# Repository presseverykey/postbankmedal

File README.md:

# POST /bank Hackathon Roadshow Medal

This repository contains hardware documentation (Eagle files and PDF) and firmware sources (C) for the medals given to winners at the POST /bank hackathon series 2016/2017 Grand Final.

The actual boards given out differ in two points:
- MCU ground connections (Pins 5 and 41) are missing on the board due to a PCB manufacturing error. They are manually routed using wire.
- Due to a worldwide supply shortage of TBD62083 drivers, the boards are populated with a TBD62003 chip (7 channels instead of 8). The remaining channel is populated with a 2N7000 NMOS on top of the TBD62003.

The board has pads for a resistive and a capacitive touch sensor, however, they are not used in the current firmware.

The firmware is based on the everykey SDK (see https://github.com/presseverykey/everykey-sdk for prerequisites, toolchain setup and more examples). Basically, an ARM GCC cross compiler and a firmware checksum tool is required. The MCU supports flashing via USB mass storage in ROM, so no additional flashing hardware is required. The firmware binary can be just copied over. To enable flashing mode, press the button while inserting the board to a USB port (add 0.5-1mm of cardboard or similar under the PCB for a stable connection). Some OSes will mount the drive directly, some require an additional reset. If required, a MCU reset can be triggered by connecting the corresponding pad of R5 to GND, e.g. using metal tweezers.

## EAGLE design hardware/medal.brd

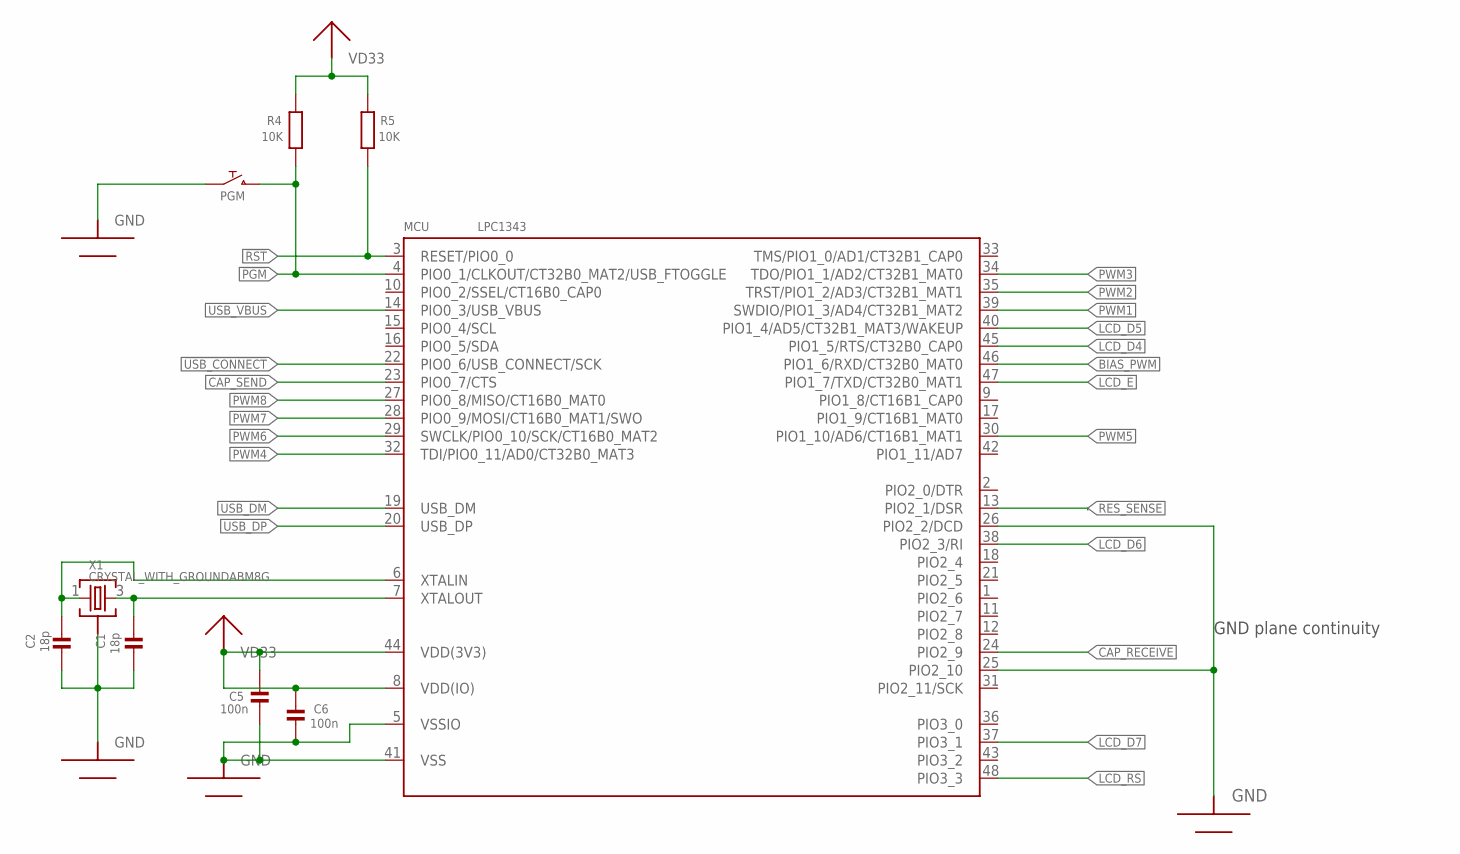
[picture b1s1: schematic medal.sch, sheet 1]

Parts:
C1, C2: 18p; 0603-NOSILK
C5, C6: 100n; 0603-NOSILK
MCU: LPC1343; QFP48-0.5-NOSILK
PGM: PUSHBUTTONKMR2XX-NOSILK; CK-KMR2-NOSILK
R4, R5: 10K; 0603-NOSILK
X1: CRYSTAL_WITH_GROUNDABM8G; ABM8G

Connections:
!PGM: MCU.4 (PIO0_1/CLKOUT/CT32B0_MAT2/USB_FTOGGLE), PGM.P$3 (2), PGM.P$4 (2), R4.1
!RST: MCU.3 (RESET/PIO0_0), R5.1
!USB_CONNECT: MCU.22 (PIO0_6/USB_CONNECT/SCK); also elsewhere on the board
BIAS_PWM: MCU.46 (PIO1_6/RXD/CT32B0_MAT0); also elsewhere on the board
CAP_RECEIVE: MCU.24 (PIO2_9); also elsewhere on the board
CAP_SEND: MCU.23 (PIO0_7/CTS); also elsewhere on the board
GND: C1.1, C2.1, C5.2, C6.2, MCU.5 (VSSIO), MCU.25 (PIO2_10), MCU.26 (PIO2_2/DCD), MCU.41 (VSS), PGM.P$1 (1), PGM.P$2 (1), X1.2 (GND), X1.4 (GND); also elsewhere on the board
LCD_D4: MCU.45 (PIO1_5/RTS/CT32B0_CAP0); also elsewhere on the board
LCD_D5: MCU.40 (PIO1_4/AD5/CT32B1_MAT3/WAKEUP); also elsewhere on the board
LCD_D6: MCU.38 (PIO2_3/RI); also elsewhere on the board
LCD_D7: MCU.37 (PIO3_1); also elsewhere on the board
LCD_E: MCU.47 (PIO1_7/TXD/CT32B0_MAT1); also elsewhere on the board
LCD_RS: MCU.48 (PIO3_3); also elsewhere on the board
unnamed: C2.2, MCU.6 (XTALIN), X1.1
unnamed: C1.2, MCU.7 (XTALOUT), X1.3 (2)
PWM1: MCU.39 (SWDIO/PIO1_3/AD4/CT32B1_MAT2); also elsewhere on the board
PWM2: MCU.35 (TRST/PIO1_2/AD3/CT32B1_MAT1); also elsewhere on the board
PWM3: MCU.34 (TDO/PIO1_1/AD2/CT32B1_MAT0); also elsewhere on the board
PWM4: MCU.32 (TDI/PIO0_11/AD0/CT32B0_MAT3); also elsewhere on the board
PWM5: MCU.30 (PIO1_10/AD6/CT16B1_MAT1); also elsewhere on the board
PWM6: MCU.29 (SWCLK/PIO0_10/SCK/CT16B0_MAT2); also elsewhere on the board
PWM7: MCU.28 (PIO0_9/MOSI/CT16B0_MAT1/SWO); also elsewhere on the board
PWM8: MCU.27 (PIO0_8/MISO/CT16B0_MAT0); also elsewhere on the board
RES_SENSE: MCU.13 (PIO2_1/DSR); also elsewhere on the board
USB_DM: MCU.19 (USB_DM); also elsewhere on the board
USB_DP: MCU.20 (USB_DP); also elsewhere on the board
USB_VBUS: MCU.14 (PIO0_3/USB_VBUS); also elsewhere on the board
VD33: C5.1, C6.1, MCU.8 (VDD(IO)), MCU.44 (VDD(3V3)), R4.2, R5.2; also elsewhere on the board

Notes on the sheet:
GND plane continuity

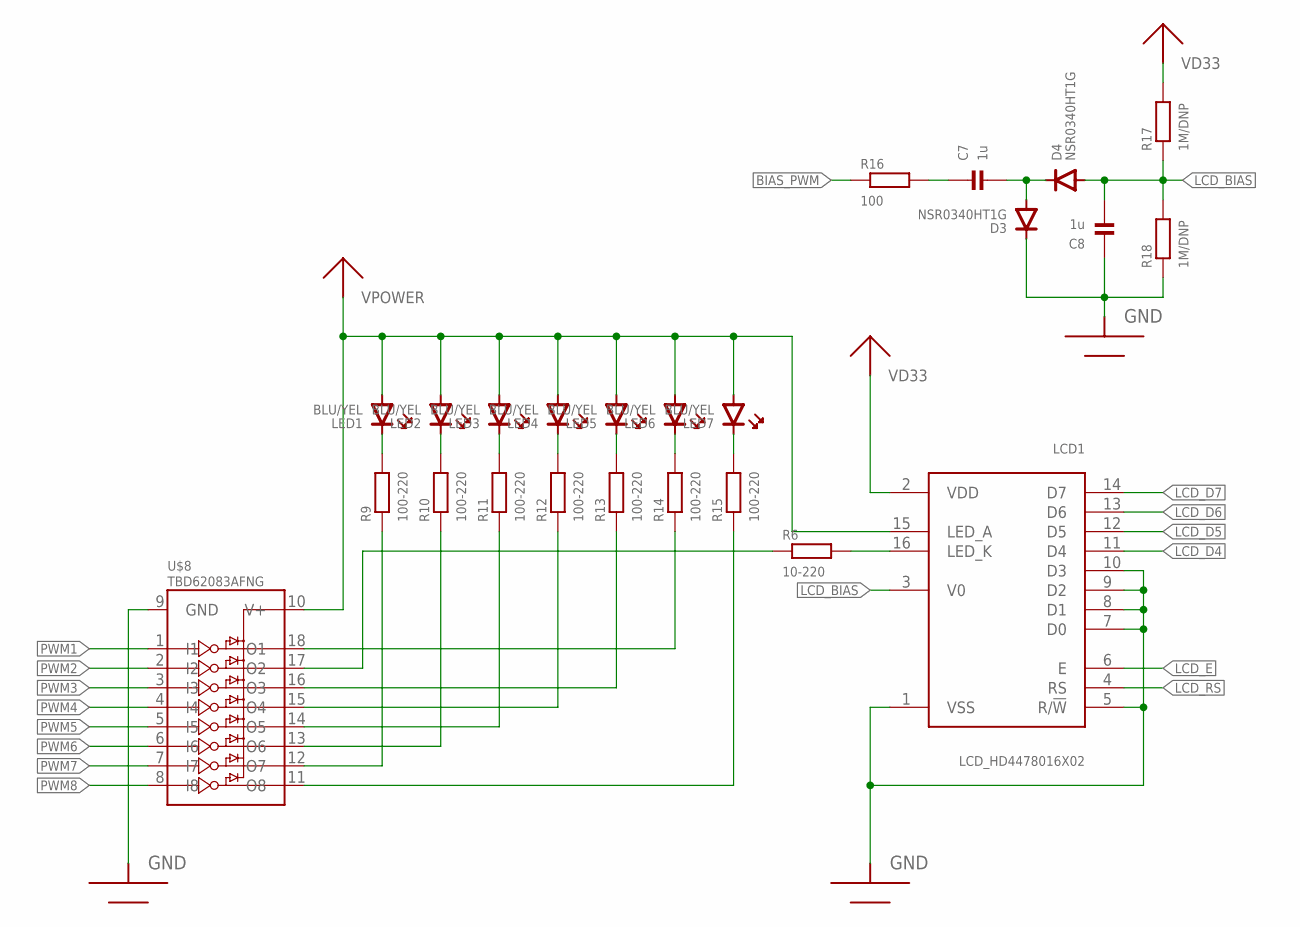
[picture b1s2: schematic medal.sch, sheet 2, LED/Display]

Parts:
C7, C8: 1u; 0603-NOSILK
D3, D4: NSR0340HT1G; SOD323R-NOPLACE
LCD1: LCD_HD4478016X02; LCD_16X02
LED1, LED2, LED3, LED4, LED5, LED6, LED7: BLU/YEL; 0603_POLAR
R6: 10-220; 1206-NOSILK
R9, R10, R11, R12, R13, R14, R15: 100-220; 0603-NOSILK
R16: 100; 0603-NOSILK
R17, R18: 1M/DNP; 0603-NOSILK
U$8: TBD62083AFNG; SSOP18-4.4-0.65-NOPLACE

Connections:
BIAS_PUMP: C7.2, D3.A (ANODE), D4.K (CATHODE)
BIAS_PWM: R16.1; also elsewhere on the board
BIAS_PWM_LIM: C7.1, R16.2
GND: C8.1, D3.K (CATHODE), LCD1.1 (VSS), LCD1.5 (R/!W), LCD1.7 (D0), LCD1.8 (D1), LCD1.9 (D2), LCD1.10 (D3), R18.1, U$8.9 (GND); also elsewhere on the board
LCD_BIAS: C8.2, D4.A (ANODE), LCD1.3 (V0), R17.1, R18.2
LCD_D4: LCD1.11 (D4); also elsewhere on the board
LCD_D5: LCD1.12 (D5); also elsewhere on the board
LCD_D6: LCD1.13 (D6); also elsewhere on the board
LCD_D7: LCD1.14 (D7); also elsewhere on the board
LCD_E: LCD1.6 (E); also elsewhere on the board
LCD_RS: LCD1.4 (RS); also elsewhere on the board
unnamed: R6.1, U$8.17 (O2)
unnamed: LCD1.16 (LED_K), R6.2
unnamed: R13.1, U$8.16 (O3)
unnamed: R10.1, U$8.13 (O6)
unnamed: LED1.K (CATHODE), R9.2
unnamed: LED2.K (CATHODE), R10.2
unnamed: LED3.K (CATHODE), R11.2
unnamed: LED4.K (CATHODE), R12.2
unnamed: LED5.K (CATHODE), R13.2
unnamed: LED6.K (CATHODE), R14.2
unnamed: LED7.K (CATHODE), R15.2
OC2: R9.1, U$8.12 (O7)
OC4: R11.1, U$8.14 (O5)
OC5: R12.1, U$8.15 (O4)
OC7: R14.1, U$8.18 (O1)
OC8: R15.1, U$8.11 (O8)
PWM1: U$8.1 (I1); also elsewhere on the board
PWM2: U$8.2 (I2); also elsewhere on the board
PWM3: U$8.3 (I3); also elsewhere on the board
PWM4: U$8.4 (I4); also elsewhere on the board
PWM5: U$8.5 (I5); also elsewhere on the board
PWM6: U$8.6 (I6); also elsewhere on the board
PWM7: U$8.7 (I7); also elsewhere on the board
PWM8: U$8.8 (I8); also elsewhere on the board
VD33: LCD1.2 (VDD), R17.2; also elsewhere on the board
VPOWER: LCD1.15 (LED_A), LED1.A (ANODE), LED2.A (ANODE), LED3.A (ANODE), LED4.A (ANODE), LED5.A (ANODE), LED6.A (ANODE), LED7.A (ANODE), U$8.10 (V+); also elsewhere on the board

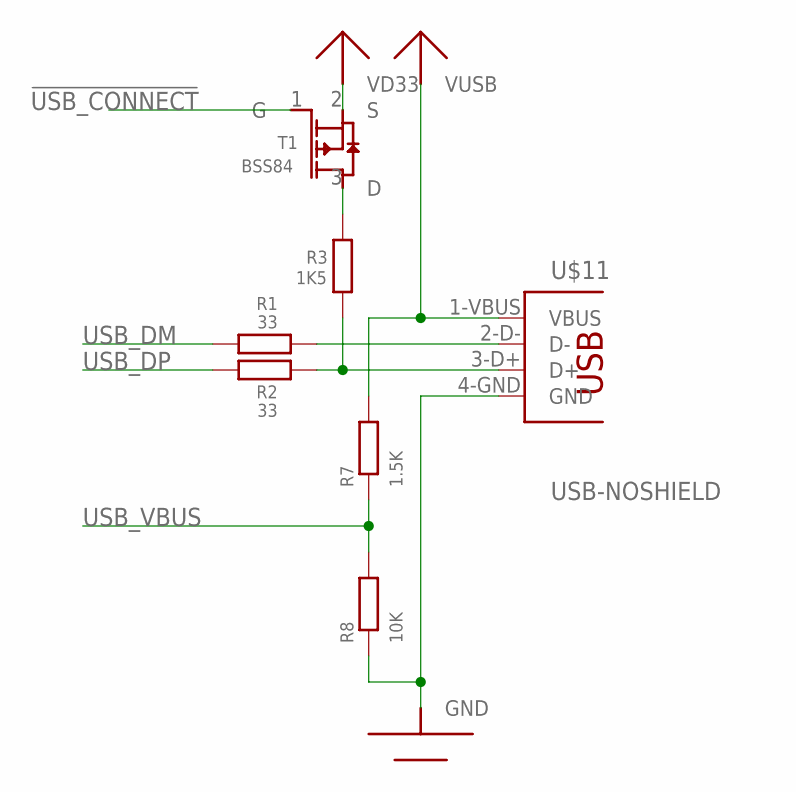
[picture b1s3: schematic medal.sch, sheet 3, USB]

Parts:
R1, R2: 33; 0603-NOSILK
R3: 1K5; 0603-NOSILK
R7: 1.5K; 0603-NOSILK
R8: 10K; 0603-NOSILK
T1: BSS84; SOT23-NOPLACE
U$11: USB-NOSHIELD; USB-A-PCB

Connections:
!USB_CONNECT: T1.1 (G); also elsewhere on the board
GND: R8.1, U$11.4-GND (GND); also elsewhere on the board
unnamed: R3.1, T1.3 (D)
USB_D+: R2.1, R3.2, U$11.3-D+ (D+)
USB_D-: R1.1, U$11.2-D- (D-)
USB_DM: R1.2; also elsewhere on the board
USB_DP: R2.2; also elsewhere on the board
USB_VBUS: R7.1, R8.2; also elsewhere on the board
VD33: T1.2 (S); also elsewhere on the board
VUSB: R7.2, U$11.1-VBUS (VBUS); also elsewhere on the board

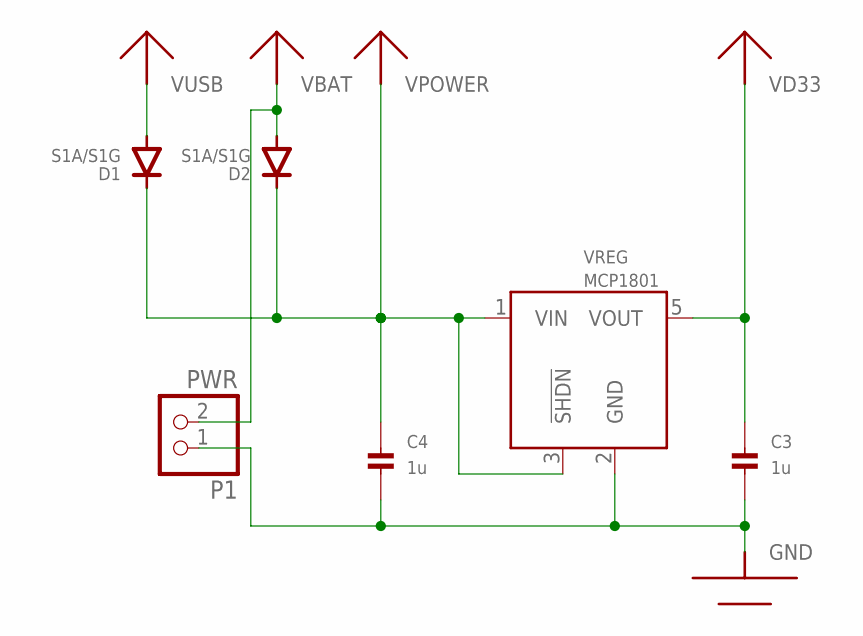
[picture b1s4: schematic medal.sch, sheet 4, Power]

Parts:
C3, C4: 1u; 0603-NOSILK
D1, D2: S1A/S1G; DSMA-NOPLACE
P1: PWR; 1X02_ROUND
VREG: MCP1801; SOT-23-5-NOSILK

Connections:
GND: C3.2, C4.2, P1.1, VREG.2 (GND); also elsewhere on the board
VBAT: D2.A (ANODE), P1.2
VD33: C3.1, VREG.5 (VOUT); also elsewhere on the board
VPOWER: C4.1, D1.C (CATHODE), D2.C (CATHODE), VREG.1 (VIN), VREG.3 (!SHDN); also elsewhere on the board
VUSB: D1.A (ANODE); also elsewhere on the board

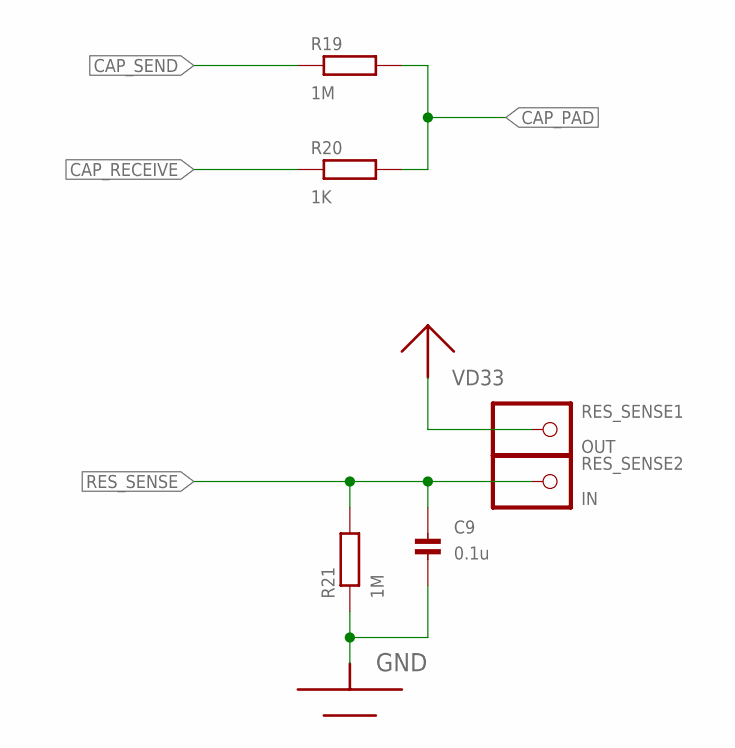
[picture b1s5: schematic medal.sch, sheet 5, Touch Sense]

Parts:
C9: 0.1u; 0603-NOSILK
R19, R21: 1M; 0603-NOSILK
R20: 1K; 0603-NOSILK
RES_SENSE1: OUT; 1X01_1MM_ROUND
RES_SENSE2: IN; 1X01_1MM_ROUND

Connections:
CAP_PAD: R19.2, R20.2
CAP_RECEIVE: R20.1; also elsewhere on the board
CAP_SEND: R19.1; also elsewhere on the board
GND: C9.2, R21.1; also elsewhere on the board
RES_SENSE: C9.1, R21.2, RES_SENSE2.P$2; also elsewhere on the board
VD33: RES_SENSE1.P$2; also elsewhere on the board

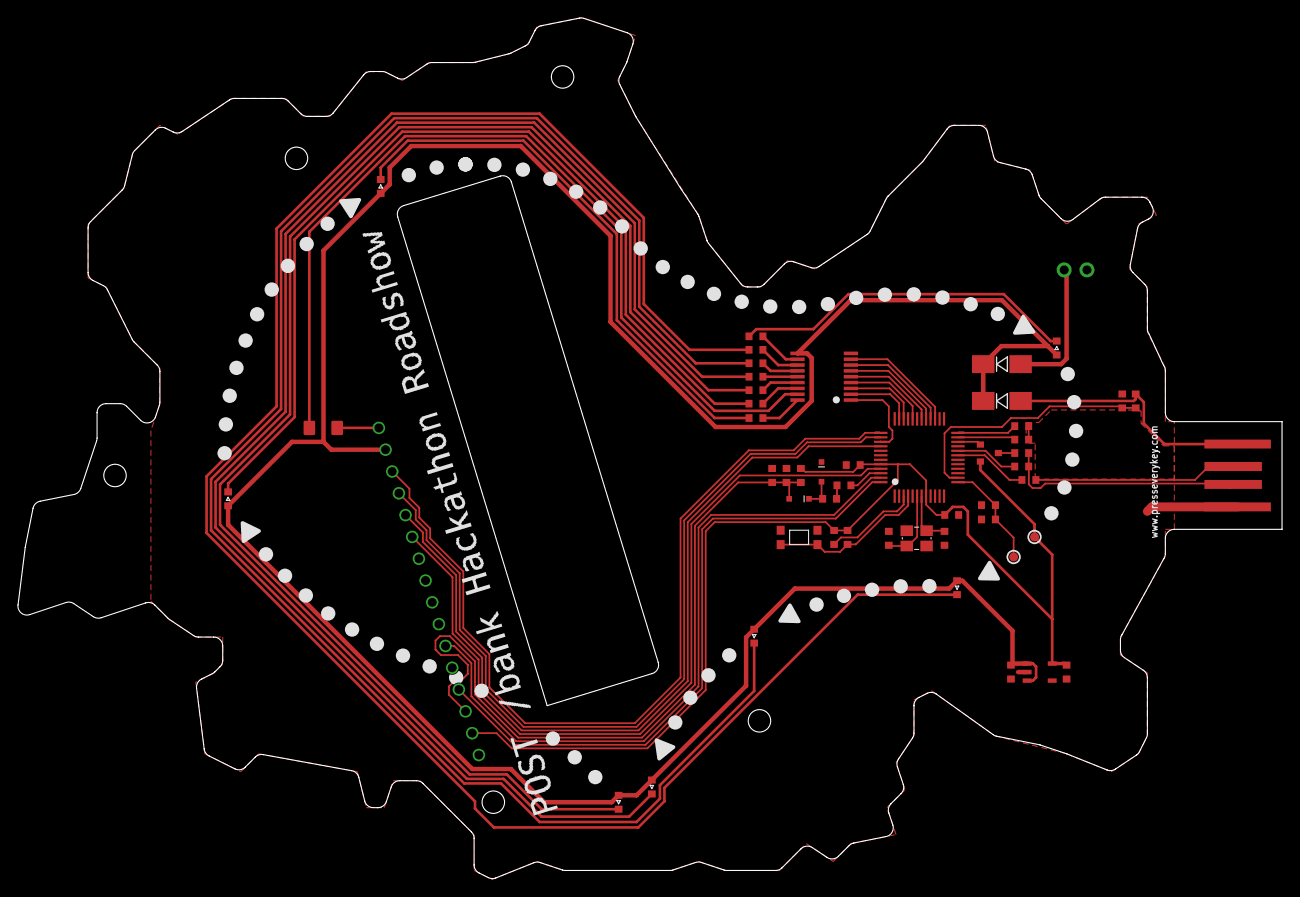
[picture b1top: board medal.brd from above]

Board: 2 copper layers, 140.8 x 95.9 mm, 52 parts (0 on the bottom side), 54 nets.

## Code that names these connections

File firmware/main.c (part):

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#define LCDPWM_TIMER CT32B1
#define LCDPWM_MAT 1

#define LCD_RS_PORT 3
#define LCD_RS_PIN 3

#define LCD_E_PORT 1
#define LCD_E_PIN 7

#define LCD_D4_PORT 1
#define LCD_D4_PIN 5

#define LCD_D5_PORT 1
#define LCD_D5_PIN 4

#define LCD_D6_PORT 2
#define LCD_D6_PIN 3

#define LCD_D7_PORT 3
#define LCD_D7_PIN 1


/*   
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
/** writes one nibble. Should not be used from outside */
void LCD_Write4(bool rs, uint8_t value) {
    every_gpio_write(LCD_RS_PORT, LCD_RS_PIN, rs);
    every_gpio_write(LCD_D7_PORT, LCD_D7_PIN, value & 8);
    every_gpio_write(LCD_D6_PORT, LCD_D6_PIN, value & 4);
    every_gpio_write(LCD_D5_PORT, LCD_D5_PIN, value & 2);
    every_gpio_write(LCD_D4_PORT, LCD_D4_PIN, value & 1);
    
    every_gpio_write(LCD_E_PORT, LCD_E_PIN, true);
    LCD_Wait_US(1);
    
    every_gpio_write(LCD_E_PORT, LCD_E_PIN, false);
    LCD_Wait_US(1);
}

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
/** initializes the pins and configures the display to a usable state */
void LCD_Init() {
    EVERY_GPIO_SET_FUNCTION(LCD_RS_PORT, LCD_RS_PIN, PIO, ADMODE_DIGITAL);
    every_gpio_set_dir(LCD_RS_PORT, LCD_RS_PIN, OUTPUT);
    every_gpio_write(LCD_RS_PORT, LCD_RS_PIN, 0);  //RS: 0 = command, 1 = data

    EVERY_GPIO_SET_FUNCTION(LCD_E_PORT, LCD_E_PIN, PIO, ADMODE_DIGITAL);
    every_gpio_set_dir(LCD_E_PORT, LCD_E_PIN, OUTPUT);
    every_gpio_write(LCD_E_PORT, LCD_E_PIN, 0);  //E: falling edge triggers transfer

    EVERY_GPIO_SET_FUNCTION(LCD_D4_PORT, LCD_D4_PIN, PIO, IOCON_IO_ADMODE_DIGITAL);
    every_gpio_set_dir(LCD_D4_PORT, LCD_D4_PIN, OUTPUT);
    every_gpio_write(LCD_D4_PORT, LCD_D4_PIN, 0);

    EVERY_GPIO_SET_FUNCTION(LCD_D5_PORT, LCD_D5_PIN, PIO, IOCON_IO_ADMODE_DIGITAL);
    every_gpio_set_dir(LCD_D5_PORT, LCD_D5_PIN, OUTPUT);
    every_gpio_write(LCD_D5_PORT, LCD_D5_PIN, 0);

    EVERY_GPIO_SET_FUNCTION(LCD_D6_PORT, LCD_D6_PIN, PIO, IOCON_IO_ADMODE_DIGITAL);
    every_gpio_set_dir(LCD_D6_PORT, LCD_D6_PIN, OUTPUT);
    every_gpio_write(LCD_D6_PORT, LCD_D6_PIN, 0);

    EVERY_GPIO_SET_FUNCTION(LCD_D7_PORT, LCD_D7_PIN, PIO, IOCON_IO_ADMODE_DIGITAL);
    every_gpio_set_dir(LCD_D7_PORT, LCD_D7_PIN, OUTPUT);
    every_gpio_write(LCD_D7_PORT, LCD_D7_PIN, 0);

    LCD_Wait_US(40000);
    
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
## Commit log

2017-03-14 Initial version
